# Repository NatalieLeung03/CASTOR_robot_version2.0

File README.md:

# Castor

(labeled diagram with all parts)

Head

Arm

Base

## 3D printing
3D printing parts STL files
[castor 3D print](https://github.com/NatalieLeung03/castor/tree/main/castor-design-master)

parts 1-29 in PLA or ABS plastics, part 30 in TPU plastic or flex resin

### special parts
In version 2.0, parts 6,7, 10, 11, 16, 17, 28, 29 are changed. Pieza boca can be 3D printed or laser-cutted for the mouth-piece. 120mm bearing can also be printed if it is not available in the country.

[Bearing](https://github.com/NatalieLeung03/castor/tree/main/castor-design-master/bearing): 
- bolitas_estatica X 18    #static balls
- bolitas_rodamiento X 18  #bearing balls
- Rod_soporte X 1          #rod support

To assemble it, place a static piece and a spherical piece intercalated as in the image, then carefully place 3d printing piece number 19 on top to cover the small pieces. Small pieces in the bearing are not supposed to move, it is supposed that the other piece roll over the bearing with those pieces.

We encountered a problem when doing these. Since support material is used when printing rod_soporte, the balls don't fit in perfectly and we will need to clean them with sandpaper. However, it is easy to overdo, so we ended up with too much space in the bearing and more balls are needed.

Different methods are going to be tested out soon.

[Bioinspired arm module](https://github.com/NatalieLeung03/castor/tree/main/castor-design-master/bioinspired%20arm%20module):
- poleaax12 for the ax-12a motors
- poleamx106 for the mx-106t motors

Depending on the version, each motor on the arms needs one pole. Version 1.0 will need 6 poleaax12, and Version 2.0 needs 4 poleaax12 + 2 poleamx106.

[Base](https://github.com/NatalieLeung03/castor/tree/main/castor-design-master/base):
- base piece
- union nervio

### skeleton
For parts 1-7,10,11,19-25, the infill is 30% with a wall thickness of 4 passes as seen in Fig. 1. 
For parts 8,9,12-18,26-29, the percentage of infill will be 80 to 100% because these parts require high rigidity for proper operation. On the other hand, for the printing of part 30 the use of filaflex material of 700% elongation is required. The printing characteristics for this part depend on the temperature characteristics and conditions of each machine (Recommendation: perform a temperature and calibration test for these elastic materials).

Fig1

## Electronics parts
Version 2.0 only needs 1 Raspberry Pi, Pi 4 or 3 model B+.

PWM PCA 9685

Adafruit eyes 11 pins, LCD display of 7-8 pins

## Components
5 Dynamixel AX-12A + 2 Dynamixel MX-106T -> 7 Dynamixel AX-12A 
(Any other amplifier with 10W and stereo input)

## Motors 
5 servo motors on castor head (2 eyebrows, 2 corners of mouth, 1 mouth piece)
(image of CASTOR head)

7 Dynamixel AX-12A 

- Neck motor ID: 1
- Right Shoulder Roll motor ID: 2
- Right Shoulder Pitch motor ID: 3
- Right Elbow Pitch motor ID: 4
- Left Shoulder Roll motor ID: 5
- Left Shoulder Pitch motor ID: 6
- Left Elbow Pitch motor ID: 7

## Screws
- M4 hex 3cm				x2			
- M3 star 1cm				x21
- M3 hex neck 2cm			x4
- Dynamixel pulley screws		x24     #m4?
- Dynamixel neck screws			x4      #m4?
- Base screws				x4              #m4?
- M3 nuts				x30
- M4 nuts				x20
- Piston screws				x8            #they are included in the piston kit

## Outfit and infill
### Outfit
[sewing pattern](https://github.com/NatalieLeung03/castor/tree/main/Sewing%20Patterns) -- need dimensions

Sewing Pattern	Materials

1	Leather - Green Color

2	Leather - Green Color

3	Leather - Metallic Color

4	Leather - Metallic Color

5	Leather - Metallic Color

6	Leather - Metallic Color

7	Leather - Metallic Color

8	Leather - Metallic Color

9	Leather - Metallic Color

10	Leather - Metallic Color

11	Stretch Fabric - M. Navy Color

12	Leather - Metallic Color

13	Stretch Fabric - M. Navy Color

14	Stretch Fabric - M. Navy Color

15	Leather - Beige Color

16	Leather - Metallic Color

17	Leather - Metallic Color

18	Leather - Metallic Color

19	Leather - Metallic Color

20	Leather - Metallic Color

21	Leather - Metallic Color

22	Leather - Metallic Color

23	Leather - Black Color

24	Polyethylene Foam 0.5''

25	Polyethylene Foam 0.5''

### Infill
no pattern or template at the moment, only images
- Polyethylene foam (chest)
- Foam

## Power and connect
### Electronic systems and sub-system overview

### PCB and power up CASTOR
PCB is needed for the LM2956, with few other components.

CASTOR PCB is from version 1.0, created using Eagle, including schematic and board files.

Power_PCB_(LM2596_with_display) and Power_PCB_(LM2596_without_display) are version 2.0, created using Altium, including all the Gerber files.

[temp link to preview Power_PCB_(LM2596_with_display)](https://www.altium.com/viewer?token=yrjcqPPWnUKv%2FRbAUB7A97Gh)

## Code
### Web interface
Here is a shorter version of the web interface compared to version 1, and in English. 
[castor 3D print](https://github.com/NatalieLeung03/castor/tree/main/web_interface_english_int) updated 18:14 27/07/23, valid for 2 days

Future goal: improve code into better structure and implement Google speech-to-text and text-to-speech and ChatGPT API into it. In order to have a smoother conversation.

# License
[read license](https://github.com/NatalieLeung03/castor/blob/main/LICENSE.txt)

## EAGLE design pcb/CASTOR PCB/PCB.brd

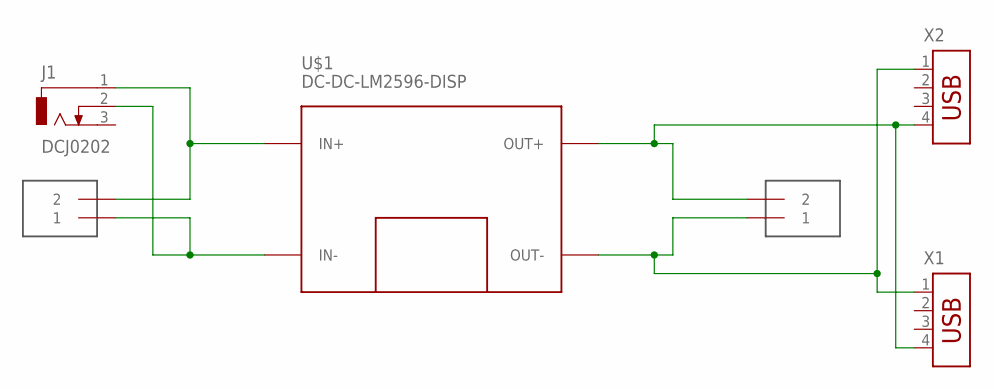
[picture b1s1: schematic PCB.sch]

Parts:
J1: DCJ0202
U$1: DC-DC-LM2596-DISP
U$2, U$3: TERMINAL_2P; KF301-2P
X1, X2: USB-787616; USB

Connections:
unnamed: J1.1, U$1.IN+, U$2.2
unnamed: J1.2, U$1.IN-, U$2.1
unnamed: U$1.OUT+, U$3.2, X1.4, X2.4
unnamed: U$1.OUT-, U$3.1, X1.1, X2.1

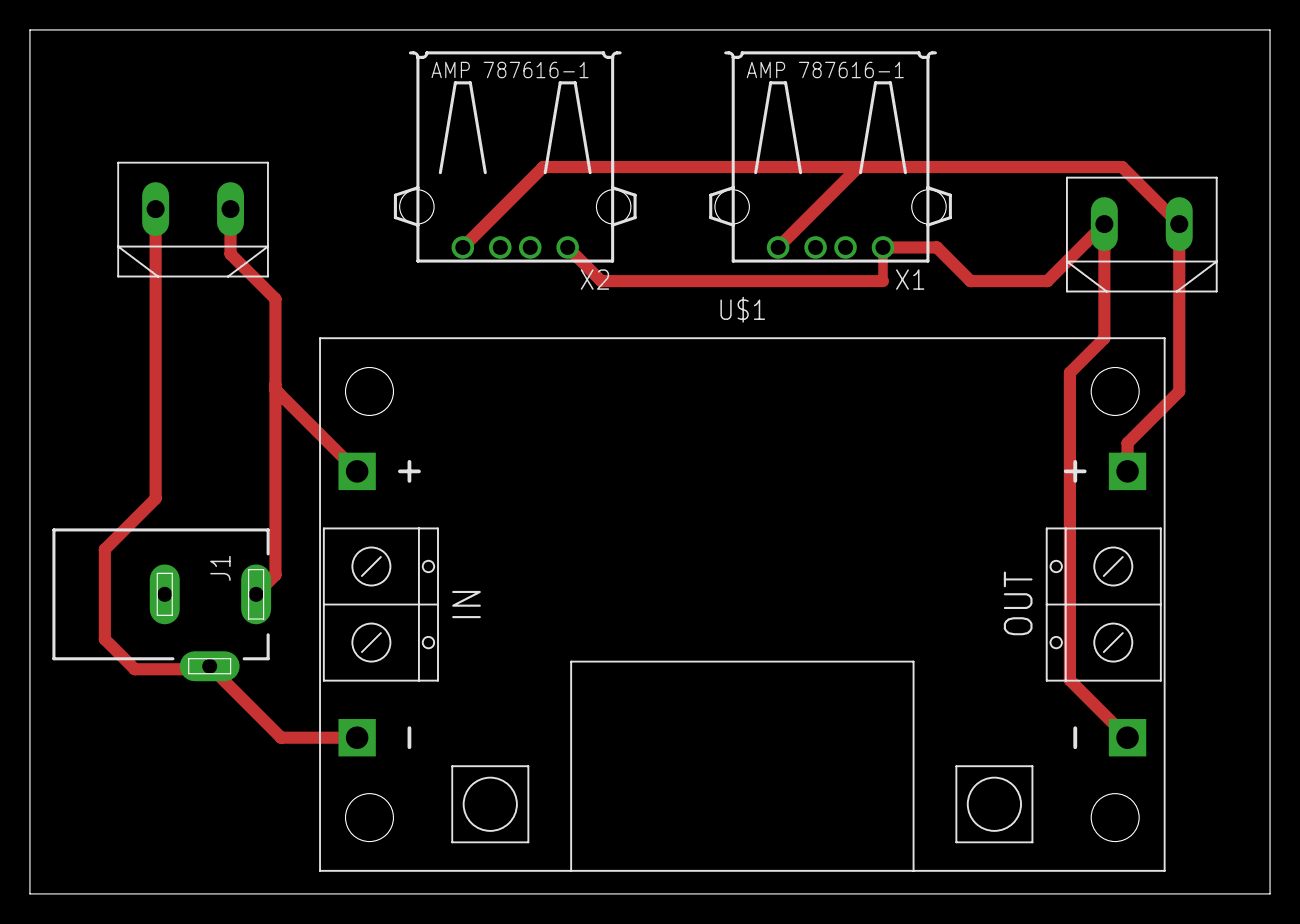
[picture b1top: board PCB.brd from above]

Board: 2 copper layers, 82.8 x 57.7 mm, 6 parts (0 on the bottom side), 4 nets.

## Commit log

2023-06-27 Add files via upload
    castor-design-3Dprinting
2023-07-27 Update README.md with PCB

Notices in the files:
parts and their libraries:
lm2596: Released under the Creative Commons Attribution 4.0 International License: http://creativecommons.org/licenses/by/4.0
